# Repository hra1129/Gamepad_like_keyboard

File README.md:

# Gamepad_like_keyboard
 キーボードのようなMSX用・SORD M5用ゲームパッド

デフォルトでは、MSX用になっています。
M5用にするためには、MSX Mode と書かれているジャンパをカットして、M5 Mode と書かれているジャンパをショートさせます。
さらに、６つのダイオードを取り付ける必要があります。

キースイッチは、こちら。
https://shop.yushakobo.jp/products/pg1350?_pos=31&_fid=22e06b805&_ss=c

キーキャップは、こちら。
https://shop.yushakobo.jp/products/mbk-choc-low-profile-keycaps?_pos=2&_sid=e73e42cb9&_ss=r

MSX用にする場合は、9pin AMPケーブルを用意して下さい。
M5用にする場合は、PS/2キーボード延長ケーブルやPS/2分岐ケーブルなどを使うのが良いです。（PS/2キーボードやマウスのケーブルは線が省略されている場合があり､その場合使えません）

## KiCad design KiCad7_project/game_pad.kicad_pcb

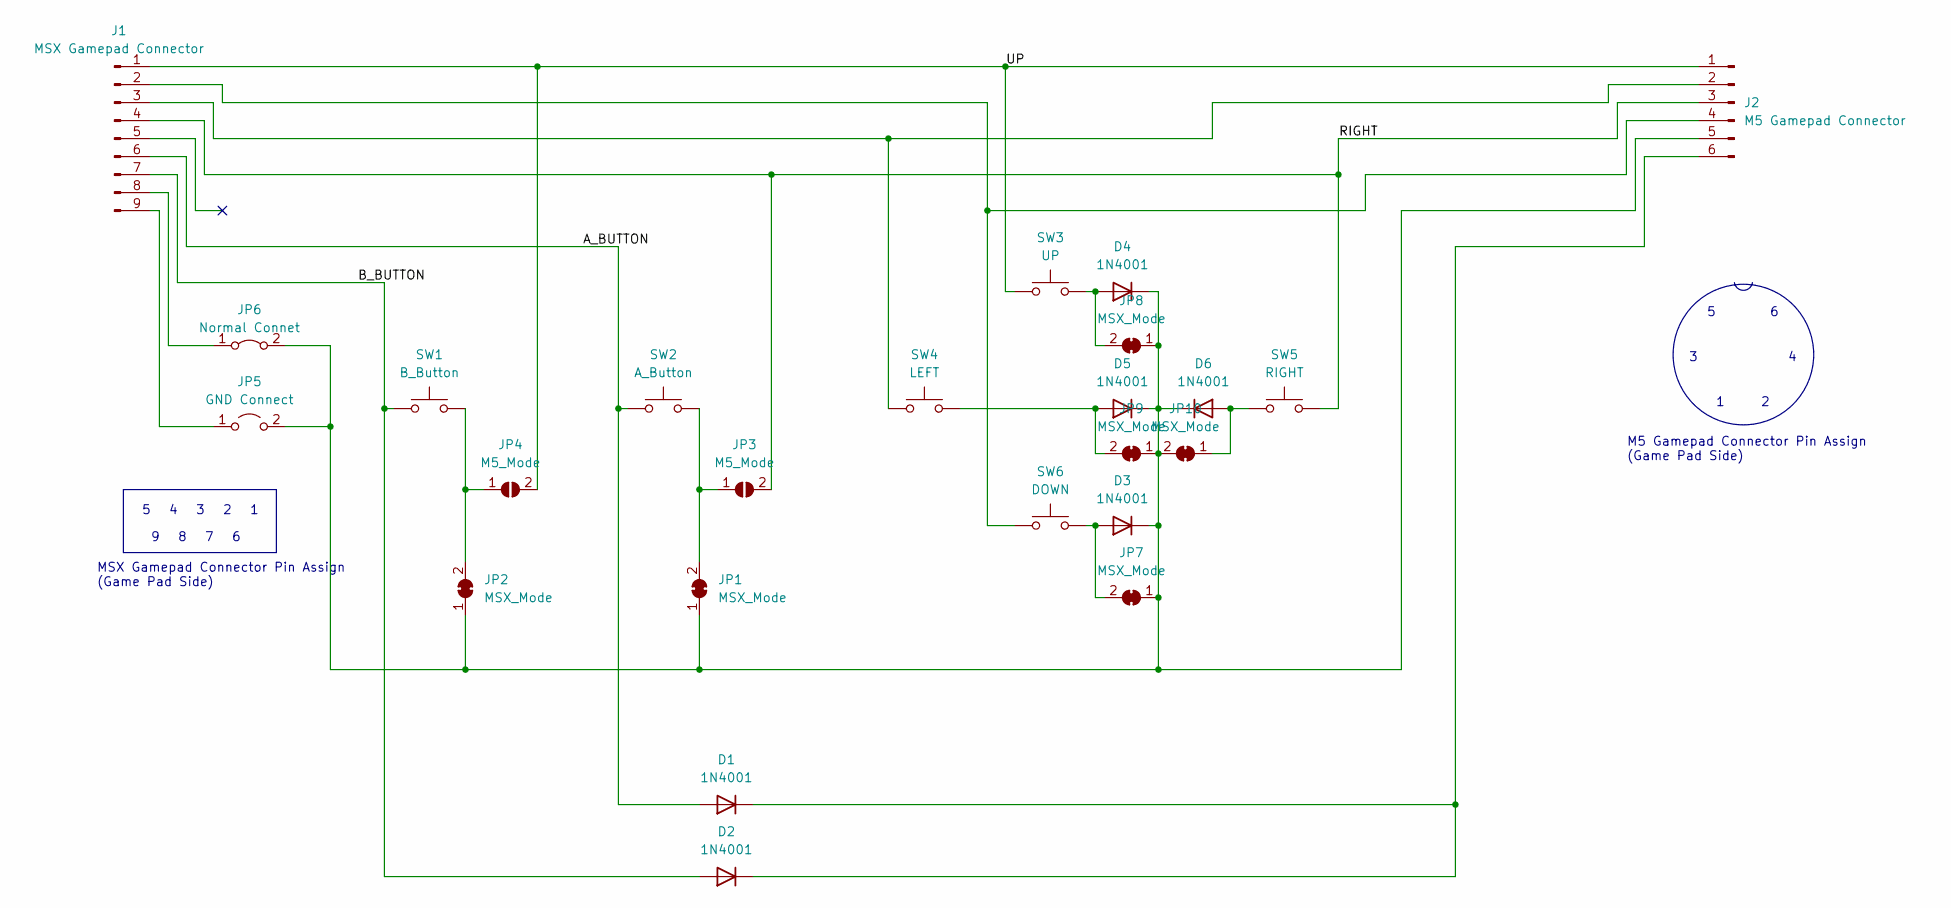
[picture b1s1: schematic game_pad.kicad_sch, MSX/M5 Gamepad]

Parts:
D1, D2, D3, D4, D5, D6: 1N4001; D_DO-41_SOD81_P10.16mm_Horizontal
J1: MSX Gamepad Connector; PinHeader_1x09_P2.54mm_Vertical
J2: M5 Gamepad Connector; PinHeader_1x06_P2.54mm_Vertical
JP1, JP2, JP7, JP8, JP9, JP10: MSX_Mode; SolderJumper-2_P1.3mm_Bridged_RoundedPad1.0x1.5mm
JP3, JP4: M5_Mode; SolderJumper-2_P1.3mm_Open_RoundedPad1.0x1.5mm
JP5: GND Connect; SolderJumper-2_P1.3mm_Open_RoundedPad1.0x1.5mm
JP6: Normal Connet; SolderJumper-2_P1.3mm_Bridged_RoundedPad1.0x1.5mm
SW1: B_Button; Kailh_Choc_V1
SW2: A_Button; Kailh_Choc_V1
SW3: UP; Kailh_Choc_V1
SW4: LEFT; Kailh_Choc_V1
SW5: RIGHT; Kailh_Choc_V1
SW6: DOWN; Kailh_Choc_V1

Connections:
/A_BUTTON: D1.2 (A), J1.6, SW2.1
/B_BUTTON: D2.2 (A), J1.7, SW1.1
/RIGHT: J1.4, J2.3, JP3.2 (B), SW5.2
/UP: J1.1, J2.1, JP4.2 (B), SW3.1
unnamed: D1.1 (K), D2.1 (K), J2.6
unnamed: D3.2 (A), JP7.2 (B), SW6.2
unnamed: D3.1 (K), D4.1 (K), D5.1 (K), D6.1 (K), J2.5, JP1.1 (A), JP2.1 (A), JP5.2 (B), JP6.2 (B), JP7.1 (A), JP8.1 (A), JP9.1 (A), JP10.2 (B)
unnamed: D4.2 (A), JP8.2 (B), SW3.2
unnamed: D5.2 (A), JP9.2 (B), SW4.2
unnamed: D6.2 (A), JP10.1 (A), SW5.1
unnamed: J1.2, J2.4, SW6.1
unnamed: J1.3, J2.2, SW4.1
unnamed: J1.8, JP6.1 (A)
unnamed: J1.9, JP5.1 (A)
unnamed: JP1.2 (B), JP3.1 (A), SW2.2
unnamed: JP2.2 (B), JP4.1 (A), SW1.2

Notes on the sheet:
M5 Gamepad Connector Pin Assign (Game Pad Side)
MSX Gamepad Connector Pin Assign (Game Pad Side)

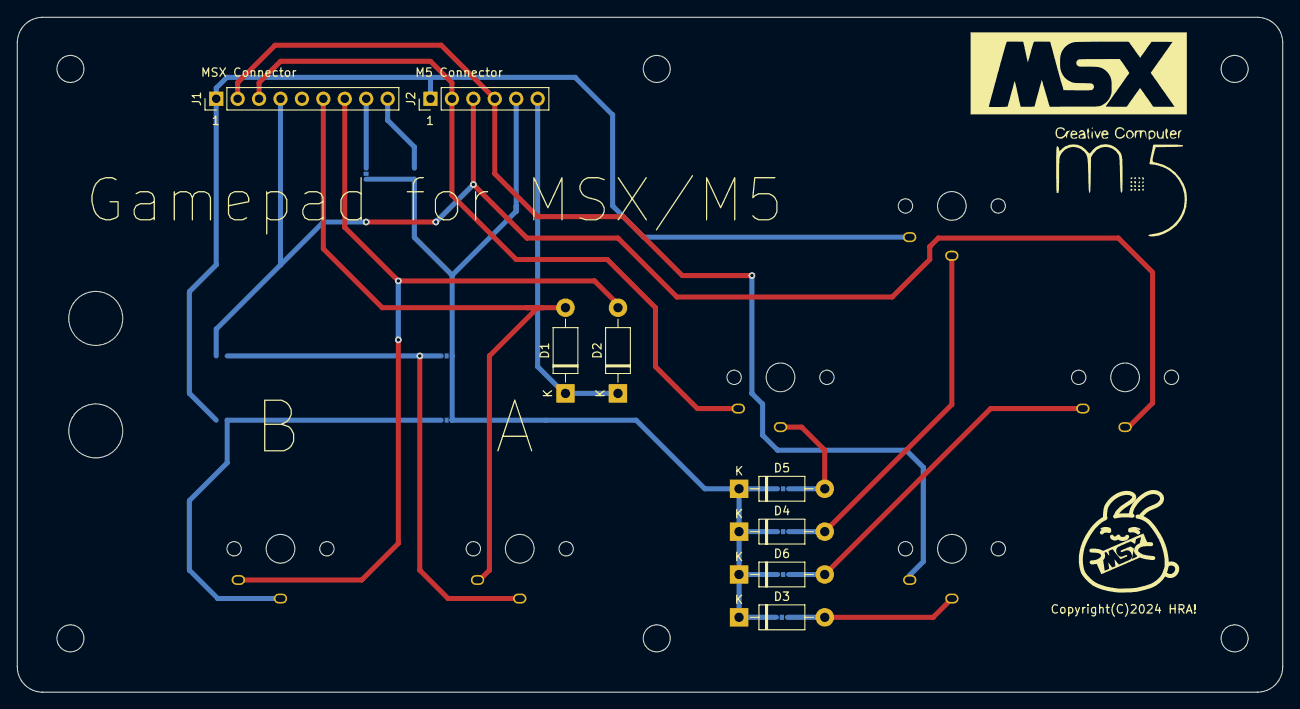
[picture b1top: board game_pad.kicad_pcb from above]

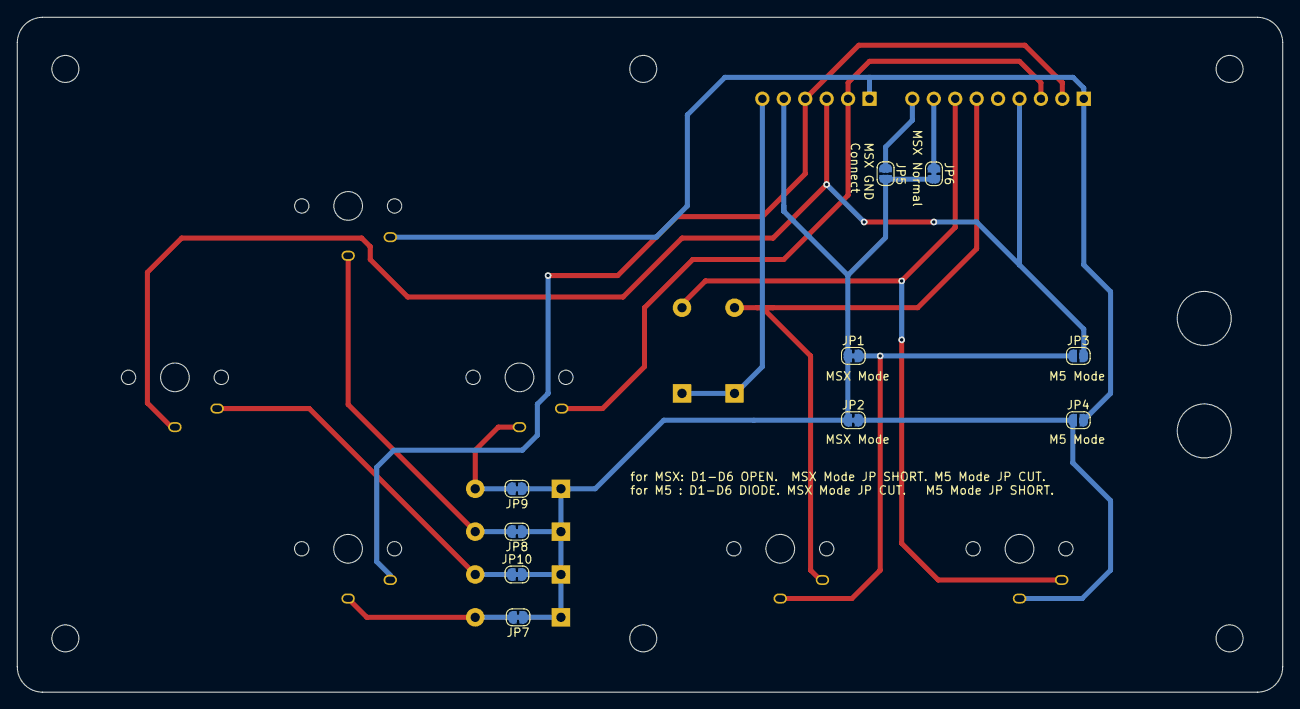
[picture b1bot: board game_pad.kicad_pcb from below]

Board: 2 copper layers, 150.0 x 80.0 mm, 32 parts (10 on the bottom side), 16 nets.

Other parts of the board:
HOLE1, HOLE2: (no value)
MH1, MH2, MH3, MH3#2, MH3#3, MH4: MountingHole_3.2mm_M3

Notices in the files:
KiCad7_project/game_pad.kicad_pcb:
Copyright(C)2024 HRA!
